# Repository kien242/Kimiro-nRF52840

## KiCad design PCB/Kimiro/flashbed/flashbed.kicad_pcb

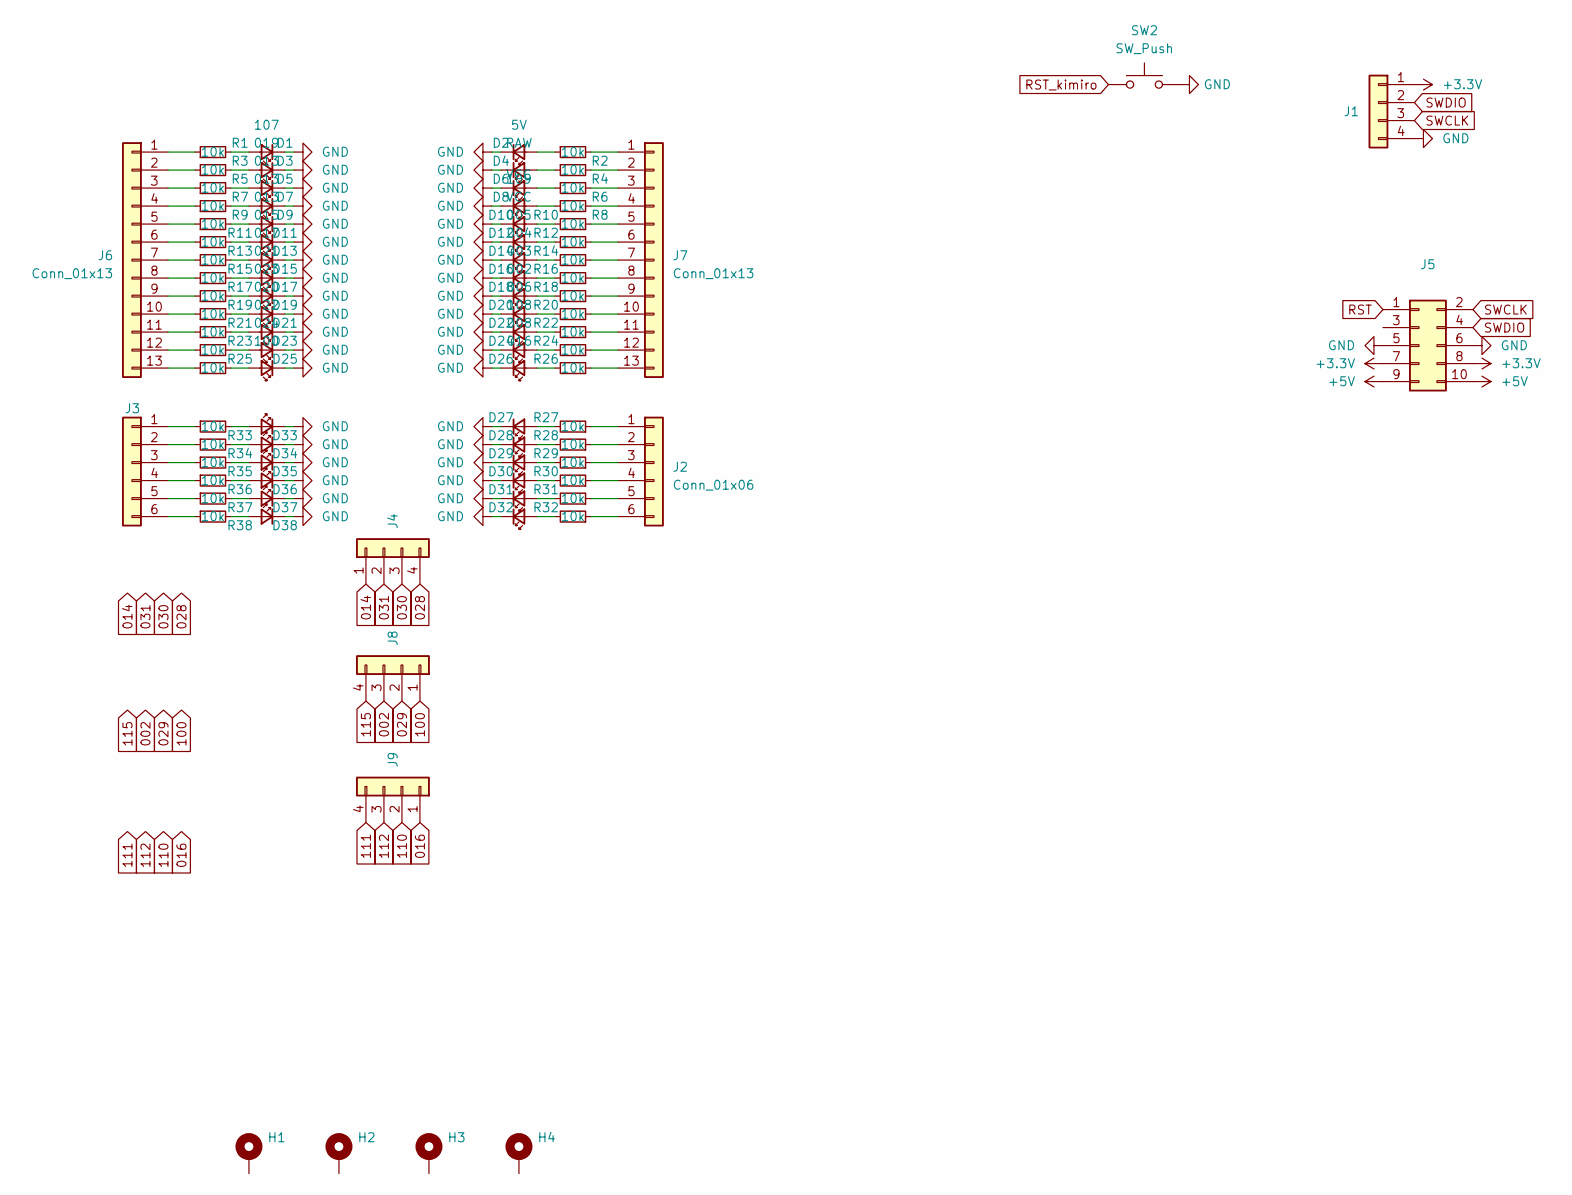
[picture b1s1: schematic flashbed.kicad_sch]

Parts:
D1: 107; LED_0603_1608Metric_Pad1.05x0.95mm_HandSolder
D2: 5V; LED_0603_1608Metric_Pad1.05x0.95mm_HandSolder
D3: 019; LED_0603_1608Metric_Pad1.05x0.95mm_HandSolder
D4: RAW; LED_0603_1608Metric_Pad1.05x0.95mm_HandSolder
D5, D7, D9: 013; LED_0603_1608Metric_Pad1.05x0.95mm_HandSolder
D6, D10: VCC; LED_0603_1608Metric_Pad1.05x0.95mm_HandSolder
D8: 109; LED_0603_1608Metric_Pad1.05x0.95mm_HandSolder
D11: 015; LED_0603_1608Metric_Pad1.05x0.95mm_HandSolder
D12: 005; LED_0603_1608Metric_Pad1.05x0.95mm_HandSolder
D13: 017; LED_0603_1608Metric_Pad1.05x0.95mm_HandSolder
D14: 004; LED_0603_1608Metric_Pad1.05x0.95mm_HandSolder
D15: 021; LED_0603_1608Metric_Pad1.05x0.95mm_HandSolder
D16: 003; LED_0603_1608Metric_Pad1.05x0.95mm_HandSolder
D17: 023; LED_0603_1608Metric_Pad1.05x0.95mm_HandSolder
D18: 002; LED_0603_1608Metric_Pad1.05x0.95mm_HandSolder
D19: 020; LED_0603_1608Metric_Pad1.05x0.95mm_HandSolder
D20: 006; LED_0603_1608Metric_Pad1.05x0.95mm_HandSolder
D21: 022; LED_0603_1608Metric_Pad1.05x0.95mm_HandSolder
D22: 108; LED_0603_1608Metric_Pad1.05x0.95mm_HandSolder
D23: 024; LED_0603_1608Metric_Pad1.05x0.95mm_HandSolder
D24: 008; LED_0603_1608Metric_Pad1.05x0.95mm_HandSolder
D25: 100; LED_0603_1608Metric_Pad1.05x0.95mm_HandSolder
D26: 016; LED_0603_1608Metric_Pad1.05x0.95mm_HandSolder
D27, D28, D29, D30, D31, D32, D33, D34, D35, D36, D37, D38: LED_0603_1608Metric_Pad1.05x0.95mm_HandSolder
H1, H2, H3, H4: MountingHole_3.2mm_M3_Pad_Via
J1, J4, J8, J9: PinHeader_1x04_P2.54mm_Vertical_P75-B1
J2: Conn_01x06; PinHeader_1x06_P2.54mm_Vertical
J3: PinHeader_1x06_P2.54mm_Vertical
J5: IDC-Header_2x05_P2.54mm_Horizontal
J6, J7: Conn_01x13; PinHeader_1x13_P2.54mm_Vertical
R1, R2, R3, R4, R5, R6, R7, R8, R9, R10, R11, R12, R13, R14, R15, R16, R17, R18, R19, R20, R21, R22, R23, R24, R25, R26, R27, R28, R29, R30, R31, R32, R33, R34, R35, R36, R37, R38: 10k; R_0603_1608Metric_Pad0.98x0.95mm_HandSolder
SW2: SW_Push; SW_SPST_TL3342

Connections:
002: J8.3
014: J4.1
016: J9.1
028: J4.4
029: J8.2
030: J4.3
031: J4.2
100: J8.1
110: J9.2
111: J9.4
112: J9.3
115: J8.4
+3V3: J1.1, J5.7, J5.8
+5V: J5.9, J5.10
GND: D1.1 (K), D2.1 (K), D3.1 (K), D4.1 (K), D5.1 (K), D6.1 (K), D7.1 (K), D8.1 (K), D9.1 (K), D10.1 (K), D11.1 (K), D12.1 (K), D13.1 (K), D14.1 (K), D15.1 (K), D16.1 (K), D17.1 (K), D18.1 (K), D19.1 (K), D20.1 (K), D21.1 (K), D22.1 (K), D23.1 (K), D24.1 (K), D25.1 (K), D26.1 (K), D27.1 (K), D28.1 (K), D29.1 (K), D30.1 (K), D31.1 (K), D32.1 (K), D33.1 (K), D34.1 (K), D35.1 (K), D36.1 (K), D37.1 (K), D38.1 (K), J1.4, J5.5, J5.6, SW2.2
unnamed: D1.2 (A), R1.2
unnamed: D2.2 (A), R2.1
unnamed: D3.2 (A), R3.2
unnamed: D4.2 (A), R4.1
unnamed: D5.2 (A), R5.2
unnamed: D6.2 (A), R6.1
unnamed: D7.2 (A), R7.2
unnamed: D8.2 (A), R8.1
unnamed: D9.2 (A), R9.2
unnamed: D10.2 (A), R10.2
unnamed: D11.2 (A), R11.2
unnamed: D12.2 (A), R12.2
unnamed: D13.2 (A), R13.2
unnamed: D14.2 (A), R14.2
unnamed: D15.2 (A), R15.2
unnamed: D16.2 (A), R16.2
unnamed: D17.2 (A), R17.2
unnamed: D18.2 (A), R18.2
unnamed: D19.2 (A), R19.2
unnamed: D20.2 (A), R20.2
unnamed: D21.2 (A), R21.2
unnamed: D22.2 (A), R22.2
unnamed: D23.2 (A), R23.2
unnamed: D24.2 (A), R24.2
unnamed: D25.2 (A), R25.2
unnamed: D26.2 (A), R26.2
unnamed: D27.2 (A), R27.2
unnamed: D28.2 (A), R28.2
unnamed: D29.2 (A), R29.2
unnamed: D30.2 (A), R30.2
unnamed: D31.2 (A), R31.2
unnamed: D32.2 (A), R32.2
unnamed: D33.2 (A), R33.2
unnamed: D34.2 (A), R34.2
unnamed: D35.2 (A), R35.2
unnamed: D36.2 (A), R36.2
unnamed: D37.2 (A), R37.2
unnamed: D38.2 (A), R38.2
unnamed: J2.1, R27.1
unnamed: J2.2, R28.1
unnamed: J2.3, R29.1
unnamed: J2.4, R30.1
unnamed: J2.5, R31.1
unnamed: J2.6, R32.1
unnamed: J3.1, R33.1
unnamed: J3.2, R34.1
unnamed: J3.3, R35.1
unnamed: J3.4, R36.1
unnamed: J3.5, R37.1
unnamed: J3.6, R38.1
unnamed: J6.1, R1.1
unnamed: J6.2, R3.1
unnamed: J6.3, R5.1
unnamed: J6.4, R7.1
unnamed: J6.5, R9.1
unnamed: J6.6, R11.1
unnamed: J6.7, R13.1
unnamed: J6.8, R15.1
unnamed: J6.9, R17.1
unnamed: J6.10, R19.1
unnamed: J6.11, R21.1
unnamed: J6.12, R23.1
unnamed: J6.13, R25.1
unnamed: J7.1, R2.2
unnamed: J7.2, R4.2
unnamed: J7.3, R6.2
unnamed: J7.4, R8.2
unnamed: J7.5, R10.1
unnamed: J7.6, R12.1
unnamed: J7.7, R14.1
unnamed: J7.8, R16.1
unnamed: J7.9, R18.1
unnamed: J7.10, R20.1
unnamed: J7.11, R22.1
unnamed: J7.12, R24.1
unnamed: J7.13, R26.1
RST: J5.1
RST_kimiro: SW2.1
SWCLK: J1.3, J5.2
SWDIO: J1.2, J5.4

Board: 2 copper layers, 129 parts (0 on the bottom side), 81 nets, no tracks yet.

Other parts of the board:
kibuzzard-62FFA9FF: G***; kibuzzard-62FFA9FF
kibuzzard-62FFAA5B, kibuzzard-62FFAA5B#2: G***; kibuzzard-62FFAA5B
kibuzzard-62FFAA07, kibuzzard-62FFAA07#2: G***; kibuzzard-62FFAA07
kibuzzard-62FFAA9F: G***; kibuzzard-62FFAA9F
kibuzzard-62FFAA43, kibuzzard-62FFAA43#2: G***; kibuzzard-62FFAA43
kibuzzard-62FFAA85: G***; kibuzzard-62FFAA85
kibuzzard-62FFAAD6, kibuzzard-62FFAAD6#2: G***; kibuzzard-62FFAAD6
kibuzzard-62FFAAE6, kibuzzard-62FFAAE6#2: G***; kibuzzard-62FFAAE6
kibuzzard-64036B7A: G***; kibuzzard-64036B7A
kibuzzard-640356F0: G***; kibuzzard-640356F0
kibuzzard-640359A3, kibuzzard-640359A3#2: G***; kibuzzard-640359A3
kibuzzard-640359AA, kibuzzard-640359AA#2: G***; kibuzzard-640359AA
kibuzzard-640359B0, kibuzzard-640359B0#2: G***; kibuzzard-640359B0
kibuzzard-640359B7: G***; kibuzzard-640359B7
kibuzzard-640359BC: G***; kibuzzard-640359BC
kibuzzard-6403595A: G***; kibuzzard-6403595A
kibuzzard-6403597E, kibuzzard-6403597E#2: G***; kibuzzard-6403597E
kibuzzard-6403599D, kibuzzard-6403599D#2: G***; kibuzzard-6403599D
kibuzzard-64035962: G***; kibuzzard-64035962
kibuzzard-64035969: G***; kibuzzard-64035969
kibuzzard-64035970: G***; kibuzzard-64035970
kibuzzard-64035979, kibuzzard-64035979#2: G***; kibuzzard-64035979
kibuzzard-64035984, kibuzzard-64035984#2: G***; kibuzzard-64035984
kibuzzard-64035989, kibuzzard-64035989#2: G***; kibuzzard-64035989
kibuzzard-64035993, kibuzzard-64035993#2: G***; kibuzzard-64035993

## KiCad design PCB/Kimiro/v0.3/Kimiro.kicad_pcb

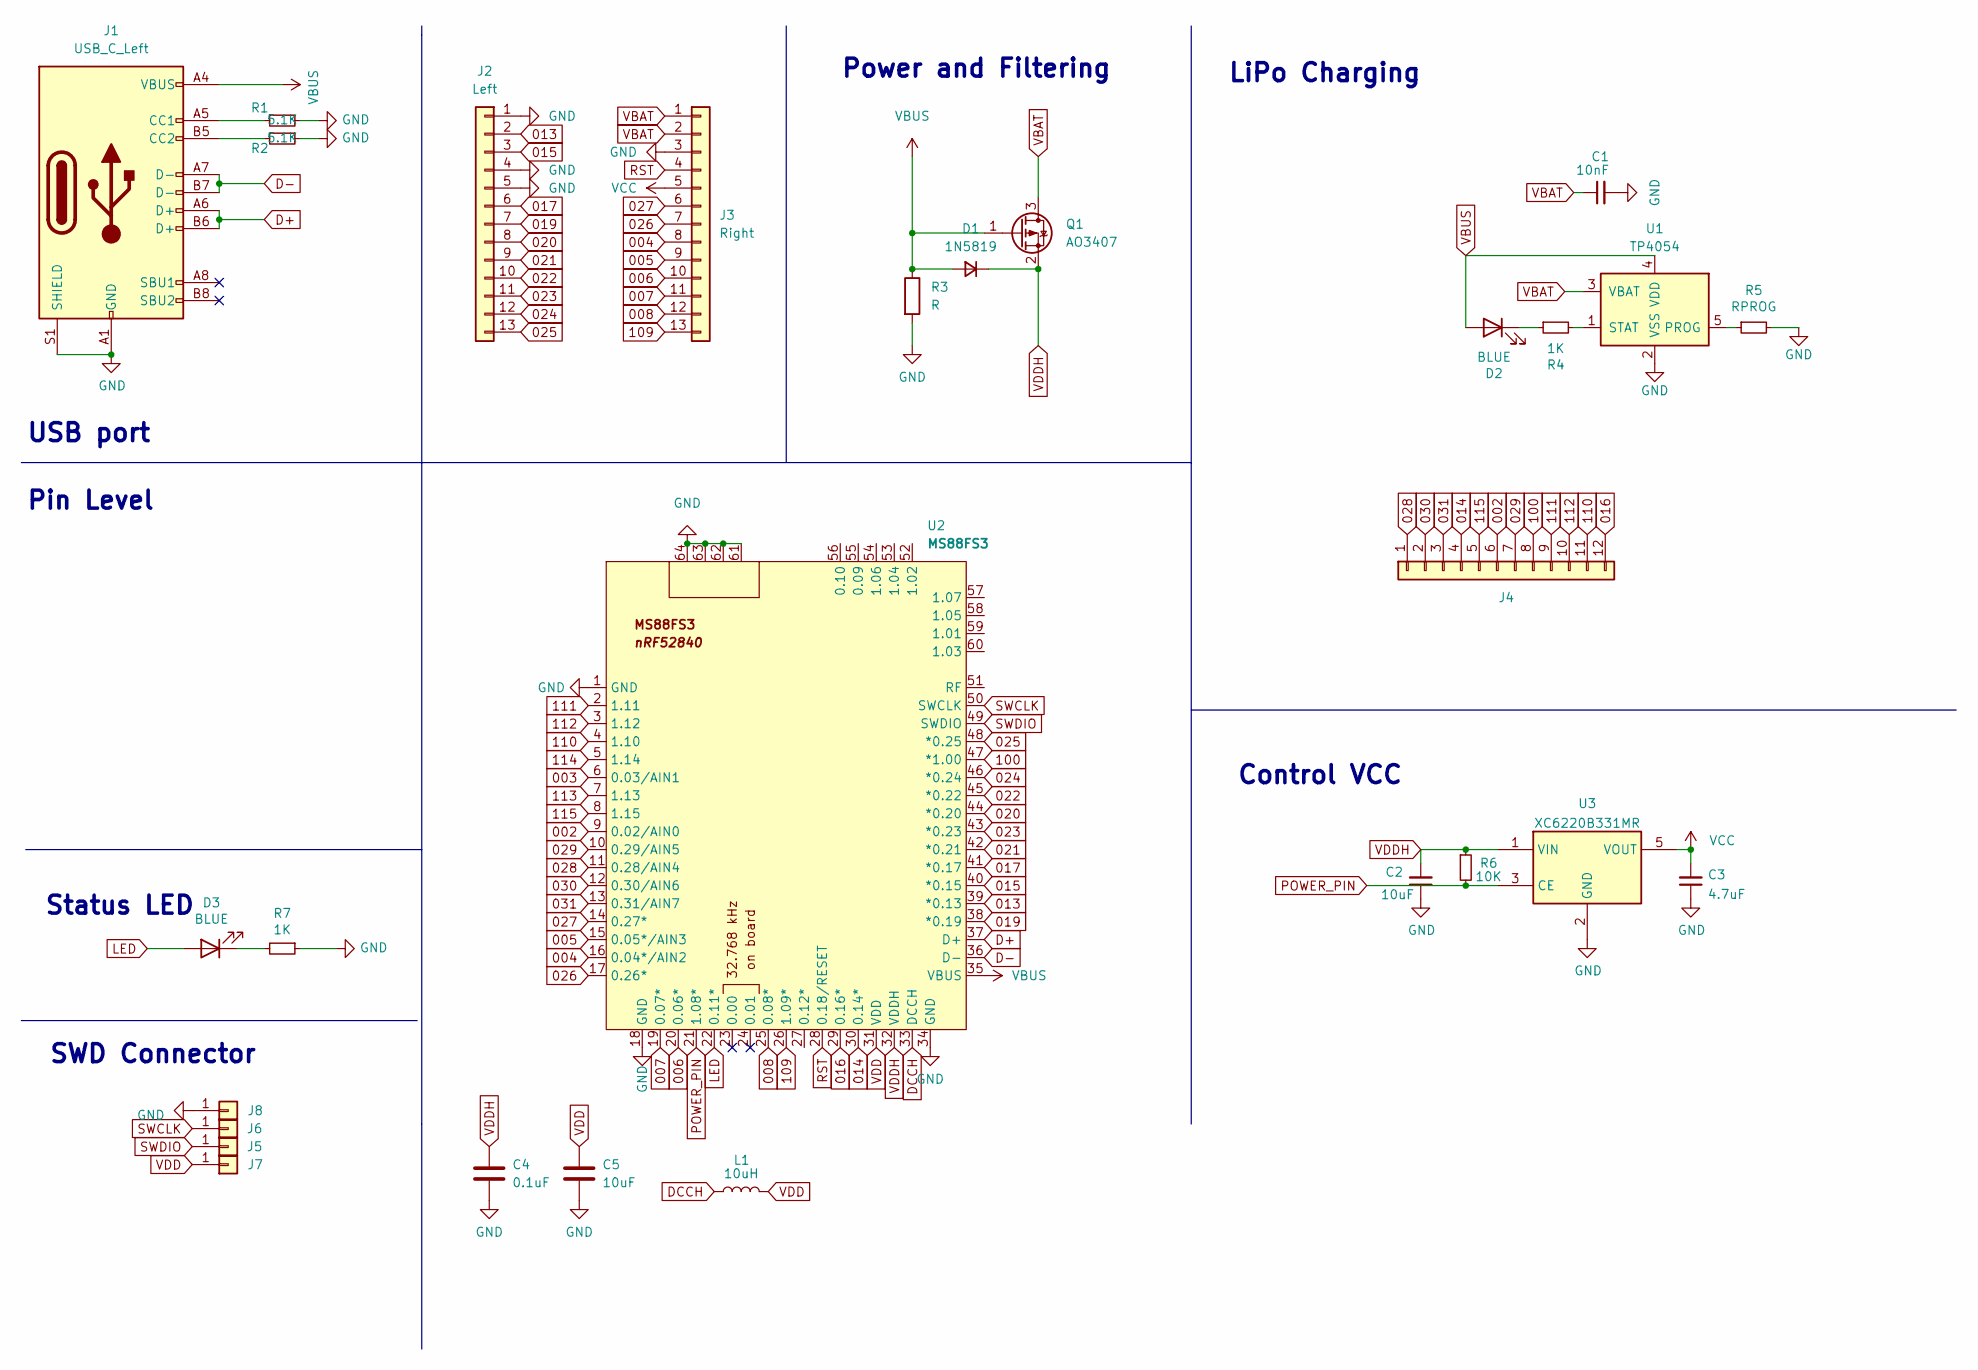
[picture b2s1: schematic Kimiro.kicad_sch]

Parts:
C1: 10nF; C_0402_1005Metric
C2: 10uF; C_0402_1005Metric; Manufacturer Part CL10A106KP8NNNC; LCSC Part C19702
C3: 4.7uF; C_0402_1005Metric; Manufacturer Part CL05A475KP5NRNC; LCSC Part C368809
C4: 0.1uF; C_0402_1005Metric
C5: 10uF; C_0402_1005Metric
D1: 1N5819; D_SOD-323
D2, D3: BLUE; LED_0603_1608Metric; LCSC Part Number C375446
J1: USB_C_Left; USB-C-Low
J2: Left; Conn_1x13_P2.54mm
J3: Right; Conn_1x13_P2.54mm
J4: Conn
J5, J6, J7, J8: Conn_1x01
L1: 10uH; L_0603_1608Metric
Q1: AO3407; SOT-23
R1, R2: 5.1K; R_0402_1005Metric
R3: R; R_0402_1005Metric
R4: 1K; R_0402_1005Metric
R5: RPROG; R_0402_1005Metric
R6: 10K; R_0402_1005Metric; Manufacturer Part RC0402FR-0710KL; LCSC Part C60490
R7: 1K; R_0402_1005Metric; LCSC Part Number C21190
U1: TP4054; SOT-23-5
U2: MS88FS3; MODULE_MS88SF3
U3: XC6220B331MR; SOT-23-5; Manufacturer Part XC6220B331MR-G‎; Digikey 893-1133-1-ND‎

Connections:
002: J4.6, U2.9 (0.02/AIN0)
003: U2.6 (0.03/AIN1)
004: J3.8, U2.16 (0.04*/AIN2)
005: J3.9, U2.15 (0.05*/AIN3)
006: J3.10, U2.20 (0.06*)
007: J3.11, U2.19 (0.07*)
008: J3.12, U2.25 (0.08*)
013: J2.2, U2.39 (*0.13)
014: J4.4, U2.30 (0.14*)
015: J2.3, U2.40 (*0.15)
016: J4.12, U2.29 (0.16*)
017: J2.6, U2.41 (*0.17)
019: J2.7, U2.38 (*0.19)
020: J2.8, U2.44 (*0.20)
021: J2.9, U2.42 (*0.21)
022: J2.10, U2.45 (*0.22)
023: J2.11, U2.43 (*0.23)
024: J2.12, U2.46 (*0.24)
025: J2.13, U2.48 (*0.25)
026: J3.7, U2.17 (0.26*)
027: J3.6, U2.14 (0.27*)
028: J4.1, U2.11 (0.28/AIN4)
029: J4.7, U2.10 (0.29/AIN5)
030: J4.2, U2.12 (0.30/AIN6)
031: J4.3, U2.13 (0.31/AIN7)
100: J4.8, U2.47 (*1.00)
109: J3.13, U2.26 (1.09*)
110: J4.11, U2.4 (1.10)
111: J4.9, U2.2 (1.11)
112: J4.10, U2.3 (1.12)
113: U2.7 (1.13)
114: U2.5 (1.14)
115: J4.5, U2.8 (1.15)
D+: J1.A6 (D+), J1.B6 (D+), U2.37 (D+)
D-: J1.A7 (D-), J1.B7 (D-), U2.36 (D-)
DCCH: L1.1, U2.33 (DCCH)
GND: C1.2, C2.1, C3.1, C4.2, C5.2, J1.A1 (GND), J1.A12 (GND), J1.B1 (GND), J1.B12 (GND), J1.S1 (SHIELD), J2.1, J2.4, J2.5, J3.3, J8.1, R1.2, R2.1, R3.2, R5.2, R7.1, U1.2 (VSS), U2.1 (GND), U2.18 (GND), U2.34 (GND), U2.61, U2.62, U2.63, U2.64, U3.2 (GND)
LED: D3.2 (A), U2.22 (0.11*)
unnamed: D2.1 (K), R4.1
unnamed: D3.1 (K), R7.2
unnamed: J1.A5 (CC1), R1.1
unnamed: J1.B5 (CC2), R2.2
unnamed: R5.1, U1.5 (PROG)
unnamed: R4.2, U1.1 (STAT)
POWER_PIN: R6.2, U2.21 (1.08*), U3.3 (CE)
RST: J3.4, U2.28 (0.18/RESET)
SWCLK: J6.1, U2.50 (SWCLK)
SWDIO: J5.1, U2.49 (SWDIO)
VBAT: C1.1, J3.1, J3.2, Q1.3 (D), U1.3 (VBAT)
VBUS: D1.2 (A), D2.2 (A), J1.A4 (VBUS), J1.A9 (VBUS), J1.B4 (VBUS), J1.B9 (VBUS), Q1.1 (G), R3.1, U1.4 (VDD), U2.35 (VBUS)
VCC: C3.2, J3.5, U3.5 (VOUT)
VDD: C5.1, J7.1, L1.2, U2.31 (VDD)
VDDH: C2.2, C4.1, D1.1 (K), Q1.2 (S), R6.1, U2.32 (VDDH), U3.1 (VIN)

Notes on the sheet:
Power and Filtering
Status LED
LiPo Charging
Control VCC
Pin Level
SWD Connector
USB port

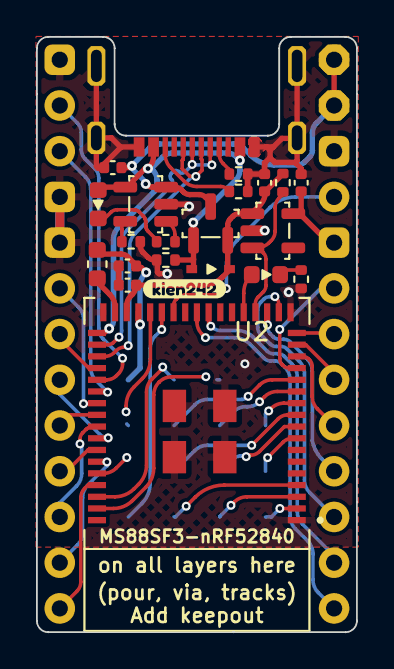
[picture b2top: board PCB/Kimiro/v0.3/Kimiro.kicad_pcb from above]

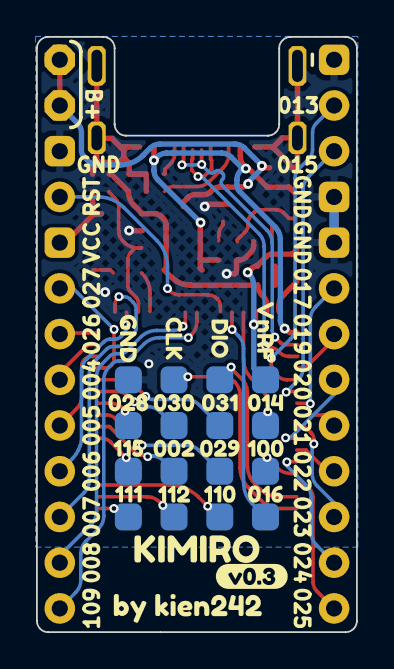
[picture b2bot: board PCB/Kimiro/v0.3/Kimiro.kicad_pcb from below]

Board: 2 copper layers, 17.8 x 33.1 mm, 48 parts (24 on the bottom side), 50 nets.

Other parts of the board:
kibuzzard-62E2A6C4: G***; kibuzzard-62E2A6C4
kibuzzard-62E24B57: G***; kibuzzard-62E24B57
kibuzzard-63BCF8A2: G***; kibuzzard-63BCF8A2
kibuzzard-63BCF8A9: G***; kibuzzard-63BCF8A9
kibuzzard-63BCF8C7: G***; kibuzzard-63BCF8C7
kibuzzard-635CB1F2: G***; kibuzzard-635CB1F1
kibuzzard-635CFC2D: G***; kibuzzard-635CFC2D
kibuzzard-635CFC3A: G***; kibuzzard-635CFC3A
kibuzzard-635CFC4F: G***; kibuzzard-635CFC4F
kibuzzard-635CFC5E: G***; kibuzzard-635CFC5E
kibuzzard-635CFC26: G***; kibuzzard-635CFC26
kibuzzard-635CFC34: G***; kibuzzard-635CFC34
kibuzzard-635CFC40: G***; kibuzzard-635CFC40
kibuzzard-635CFC48: G***; kibuzzard-635CFC48
kibuzzard-635CFC57: G***; kibuzzard-635CFC57
kibuzzard-635CFC63: G***; kibuzzard-635CFC63
kibuzzard-635CFC69: G***; kibuzzard-635CFC69
kibuzzard-635D09C5: G***; kibuzzard-635D09C5
kibuzzard-64034CD4: G***; kibuzzard-64034CD4
kibuzzard-640324C5: G***; kibuzzard-640324C5

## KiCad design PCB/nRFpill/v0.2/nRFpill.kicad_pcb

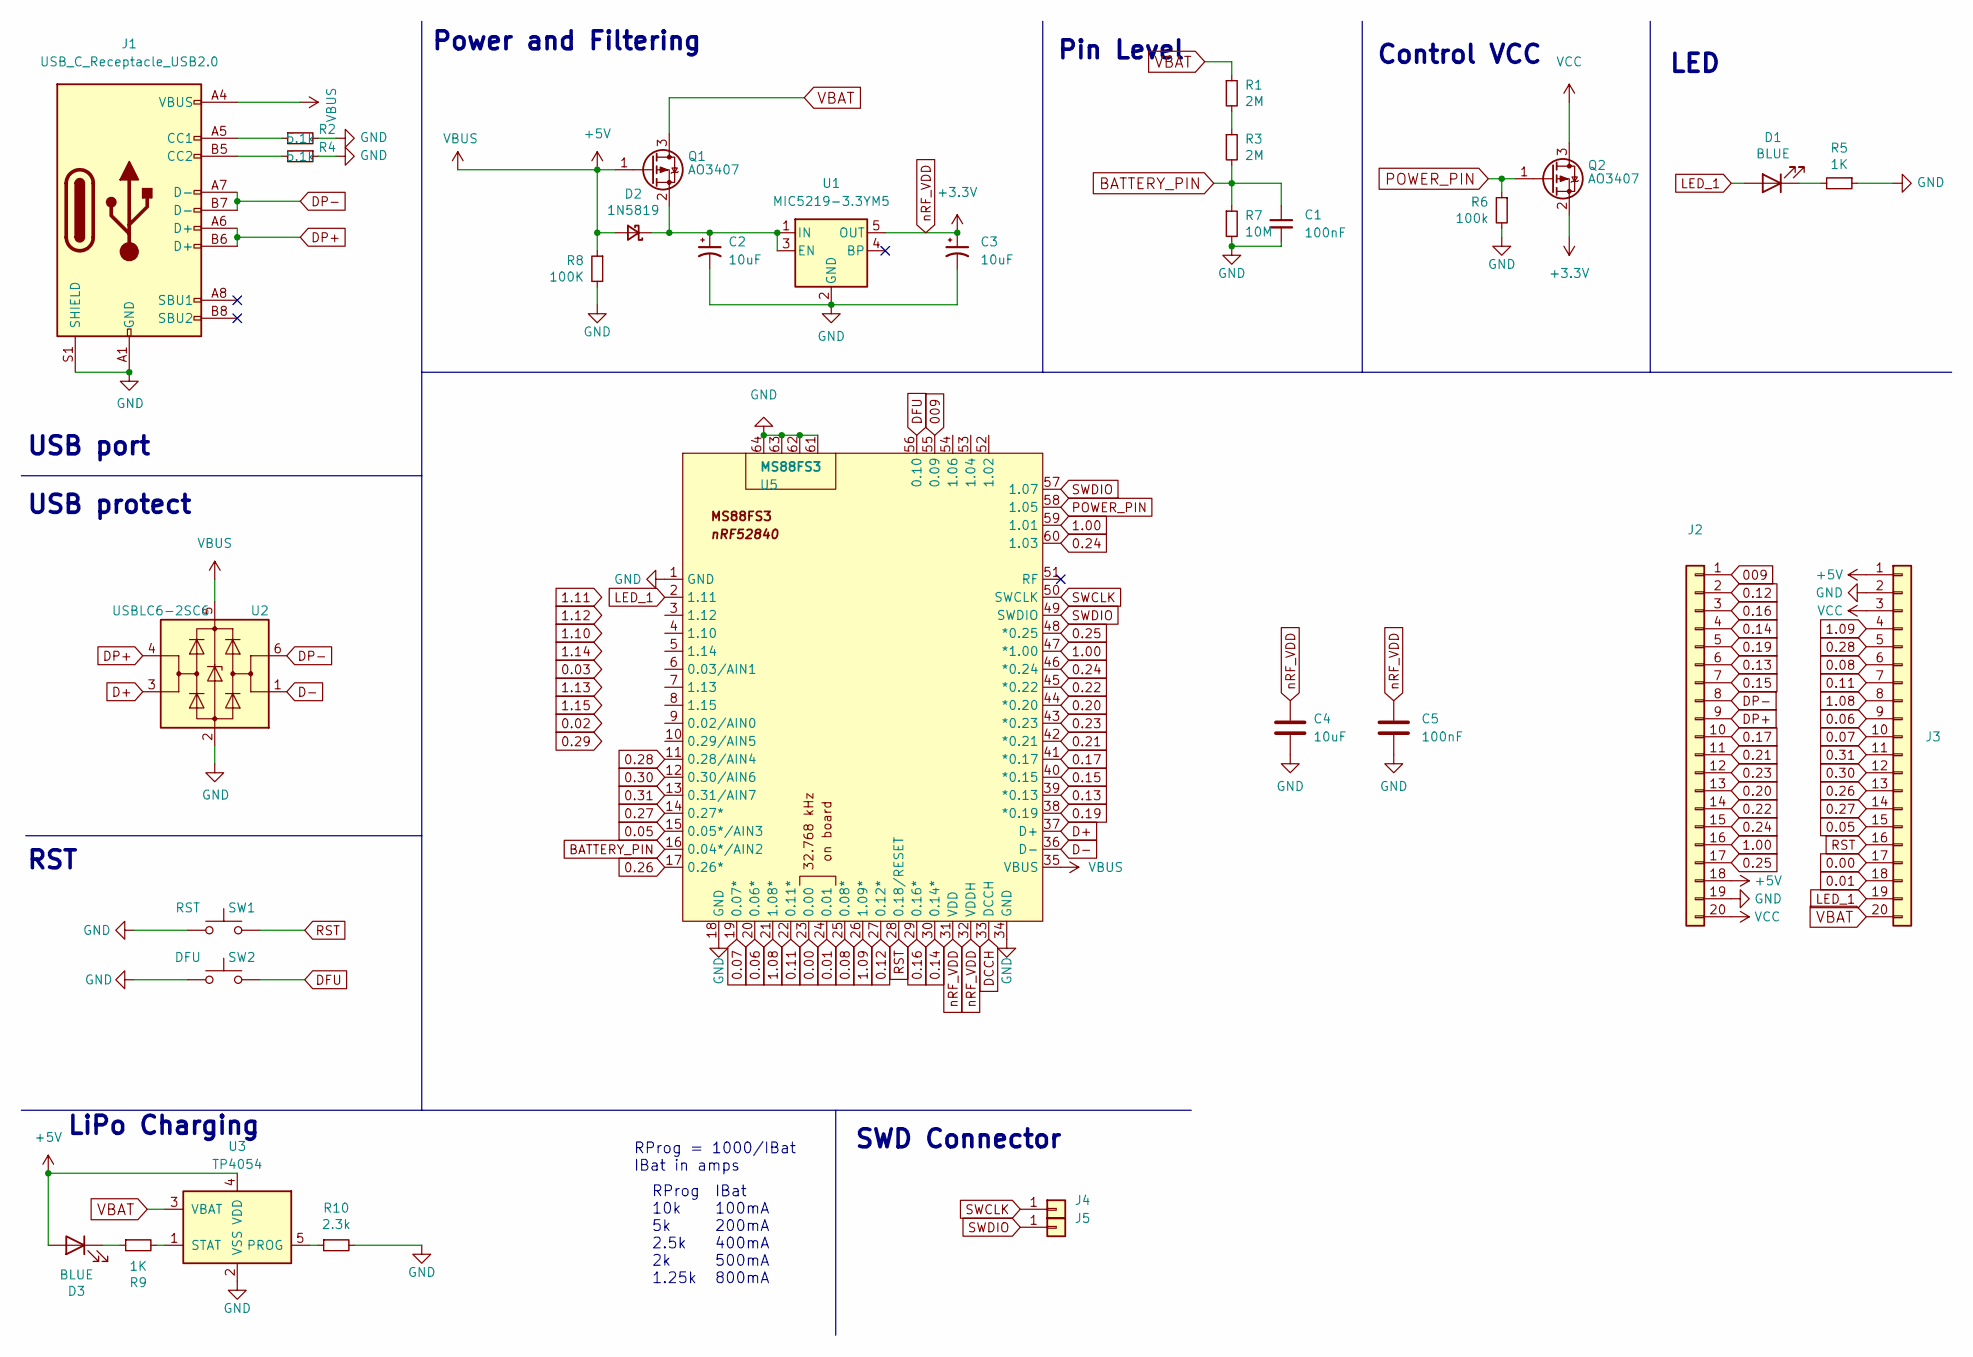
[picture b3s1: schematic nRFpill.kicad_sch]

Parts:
C1, C5: 100nF; C_0603_1608Metric
C2, C3: 10uF; CP_EIA-3216-12_Kemet-S
C4: 10uF; C_0603_1608Metric
D1, D3: BLUE; LED_0603_1608Metric; LCSC Part Number C375446
D2: 1N5819; D_SOD-323_HandSoldering
J1: USB_C_Receptacle_USB2.0; USB-C-Low
J2, J3: PinHeader_1x20_P2.54mm_Vertical
J4: TestPoint_Pad_1.5x1.5mm
J5: TestPoint_Pad_D1.5mm
Q1, Q2: AO3407; SOT-23
R1, R3: 2M; R_0603_1608Metric
R2, R4: 5.1k; R_0603_1608Metric
R5: 1K; R_0603_1608Metric; LCSC Part Number C21190
R6: 100k; R_0603_1608Metric
R7: 10M; R_0603_1608Metric
R8: 100K; R_0603_1608Metric
R9: 1K; R_0603_1608Metric
R10: 2.3k; R_0603_1608Metric
SW1: RST; SW_SPST_B3U-1000P
SW2: DFU; SW_SPST_B3U-1000P
U1: MIC5219-3.3YM5; SOT-23-5
U2: USBLC6-2SC6; SOT-23-6
U3: TP4054; SOT-23-5
U5: MS88FS3; MODULE_MS88SF3

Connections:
0.00: J3.17, U5.23 (0.00)
0.01: J3.18, U5.24 (0.01)
0.05: J3.15, U5.15 (0.05*/AIN3)
0.06: J3.9, U5.20 (0.06*)
0.07: J3.10, U5.19 (0.07*)
0.08: J3.6, U5.25 (0.08*)
0.11: J3.7, U5.22 (0.11*)
0.12: J2.2, U5.27 (0.12*)
0.13: J2.6, U5.39 (*0.13)
0.14: J2.4, U5.30 (0.14*)
0.15: J2.7, U5.40 (*0.15)
0.16: J2.3, U5.29 (0.16*)
0.17: J2.10, U5.41 (*0.17)
0.19: J2.5, U5.38 (*0.19)
0.20: J2.13, U5.44 (*0.20)
0.21: J2.11, U5.42 (*0.21)
0.22: J2.14, U5.45 (*0.22)
0.23: J2.12, U5.43 (*0.23)
0.24: J2.15, U5.46 (*0.24), U5.60 (1.03)
0.25: J2.17, U5.48 (*0.25)
0.26: J3.13, U5.17 (0.26*)
0.27: J3.14, U5.14 (0.27*)
0.28: J3.5, U5.11 (0.28/AIN4)
0.30: J3.12, U5.12 (0.30/AIN6)
0.31: J3.11, U5.13 (0.31/AIN7)
1.00: J2.16, U5.47 (*1.00), U5.59 (1.01)
1.08: J3.8, U5.21 (1.08*)
1.09: J3.4, U5.26 (1.09*)
009: J2.1, U5.55 (0.09)
+5V: D2.2 (A), D3.2 (A), J1.A4 (VBUS), J1.A9 (VBUS), J1.B4 (VBUS), J1.B9 (VBUS), J2.18, J3.1, Q1.1 (G), R8.1, U2.5 (VBUS), U3.4 (VDD), U5.35 (VBUS)
BATTERY_PIN: C1.1, R3.2, R7.1, U5.16 (0.04*/AIN2)
D+: U2.3 (I/O2), U5.37 (D+)
D-: U2.1 (I/O1), U5.36 (D-)
DCCH: U5.33 (DCCH)
DFU: SW2.2, U5.56 (0.10)
DP+: J1.A6 (D+), J1.B6 (D+), J2.9, U2.4 (I/O2)
DP-: J1.A7 (D-), J1.B7 (D-), J2.8, U2.6 (I/O1)
GND: C1.2, C2.2, C3.2, C4.2, C5.2, J1.A1 (GND), J1.A12 (GND), J1.B1 (GND), J1.B12 (GND), J1.S1 (SHIELD), J2.19, J3.2, R2.2, R4.1, R5.1, R6.2, R7.2, R8.2, R10.2, SW1.1, SW2.1, U1.2 (GND), U2.2 (GND), U3.2 (VSS), U5.1 (GND), U5.18 (GND), U5.34 (GND), U5.61, U5.62, U5.63, U5.64
LED_1: D1.2 (A), J3.19, U5.2 (1.11)
unnamed: C2.1, D2.1 (K), Q1.2 (S), U1.1 (IN), U1.3 (EN)
unnamed: D1.1 (K), R5.2
unnamed: D3.1 (K), R9.1
unnamed: J1.A5 (CC1), R2.1
unnamed: J1.B5 (CC2), R4.2
unnamed: R1.2, R3.1
unnamed: R9.2, U3.1 (STAT)
unnamed: R10.1, U3.5 (PROG)
POWER_PIN: Q2.1 (G), R6.1, U5.58 (1.05)
RST: J3.16, SW1.2, U5.28 (0.18/RESET)
SWCLK: J4.1, U5.50 (SWCLK)
SWDIO: J5.1, U5.49 (SWDIO), U5.57 (1.07)
VBAT: J3.20, Q1.3 (D), R1.1, U3.3 (VBAT)
VCC: J2.20, J3.3, Q2.3 (D)
nRF_VDD: C3.1, C4.1, C5.1, Q2.2 (S), U1.5 (OUT), U5.31 (VDD), U5.32 (VDDH)

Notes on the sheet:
Control VCC
RProg 10k 5k 2.5k 2k 1.25k
RST
RProg = 1000/IBat IBat in amps
LED
Power and Filtering
USB protect
IBat 100mA 200mA 400mA 500mA 800mA
LiPo Charging
USB port
Pin Level
SWD Connector

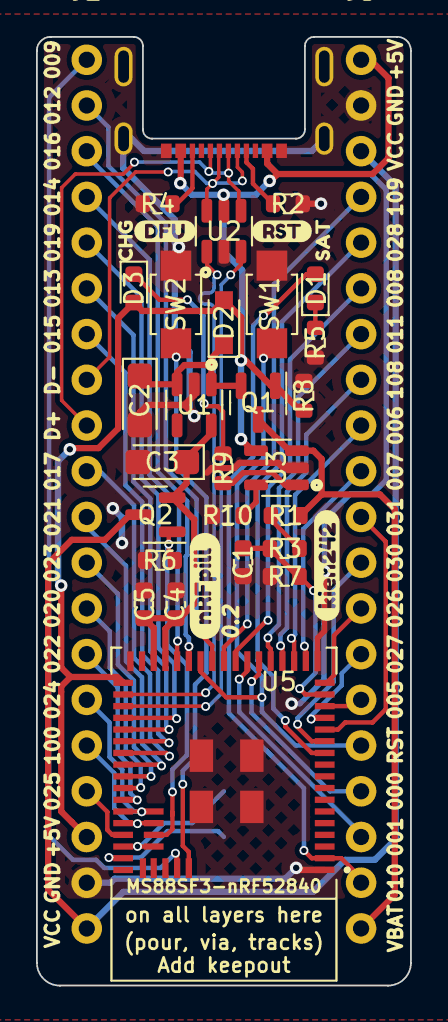
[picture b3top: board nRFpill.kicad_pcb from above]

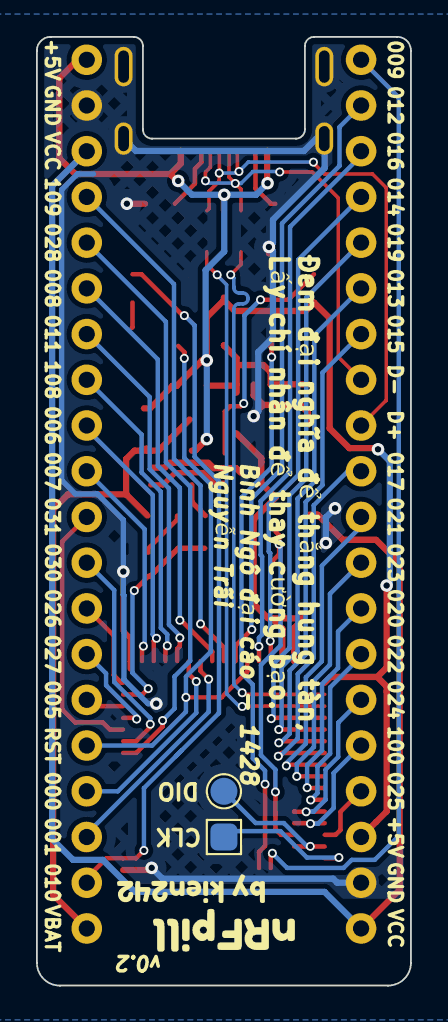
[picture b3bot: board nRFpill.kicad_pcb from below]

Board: 2 copper layers, 20.8 x 52.7 mm, 39 parts (4 on the bottom side), 53 nets.

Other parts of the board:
kibuzzard-62FEE3AB: G***; kibuzzard-62FEE3AB
kibuzzard-62FEE358: G***; kibuzzard-62FEE358
kibuzzard-6303CF12: G***; kibuzzard-6303CF12
kibuzzard-6303CF50: G***; kibuzzard-6303CF50
kibuzzard-6303CFD4: G***; kibuzzard-6303CFD4
kibuzzard-6303D094: G***; kibuzzard-6303D094
kibuzzard-63049CD9: G***; kibuzzard-63049CD9
kibuzzard-63049CF8: G***; kibuzzard-63049CF8

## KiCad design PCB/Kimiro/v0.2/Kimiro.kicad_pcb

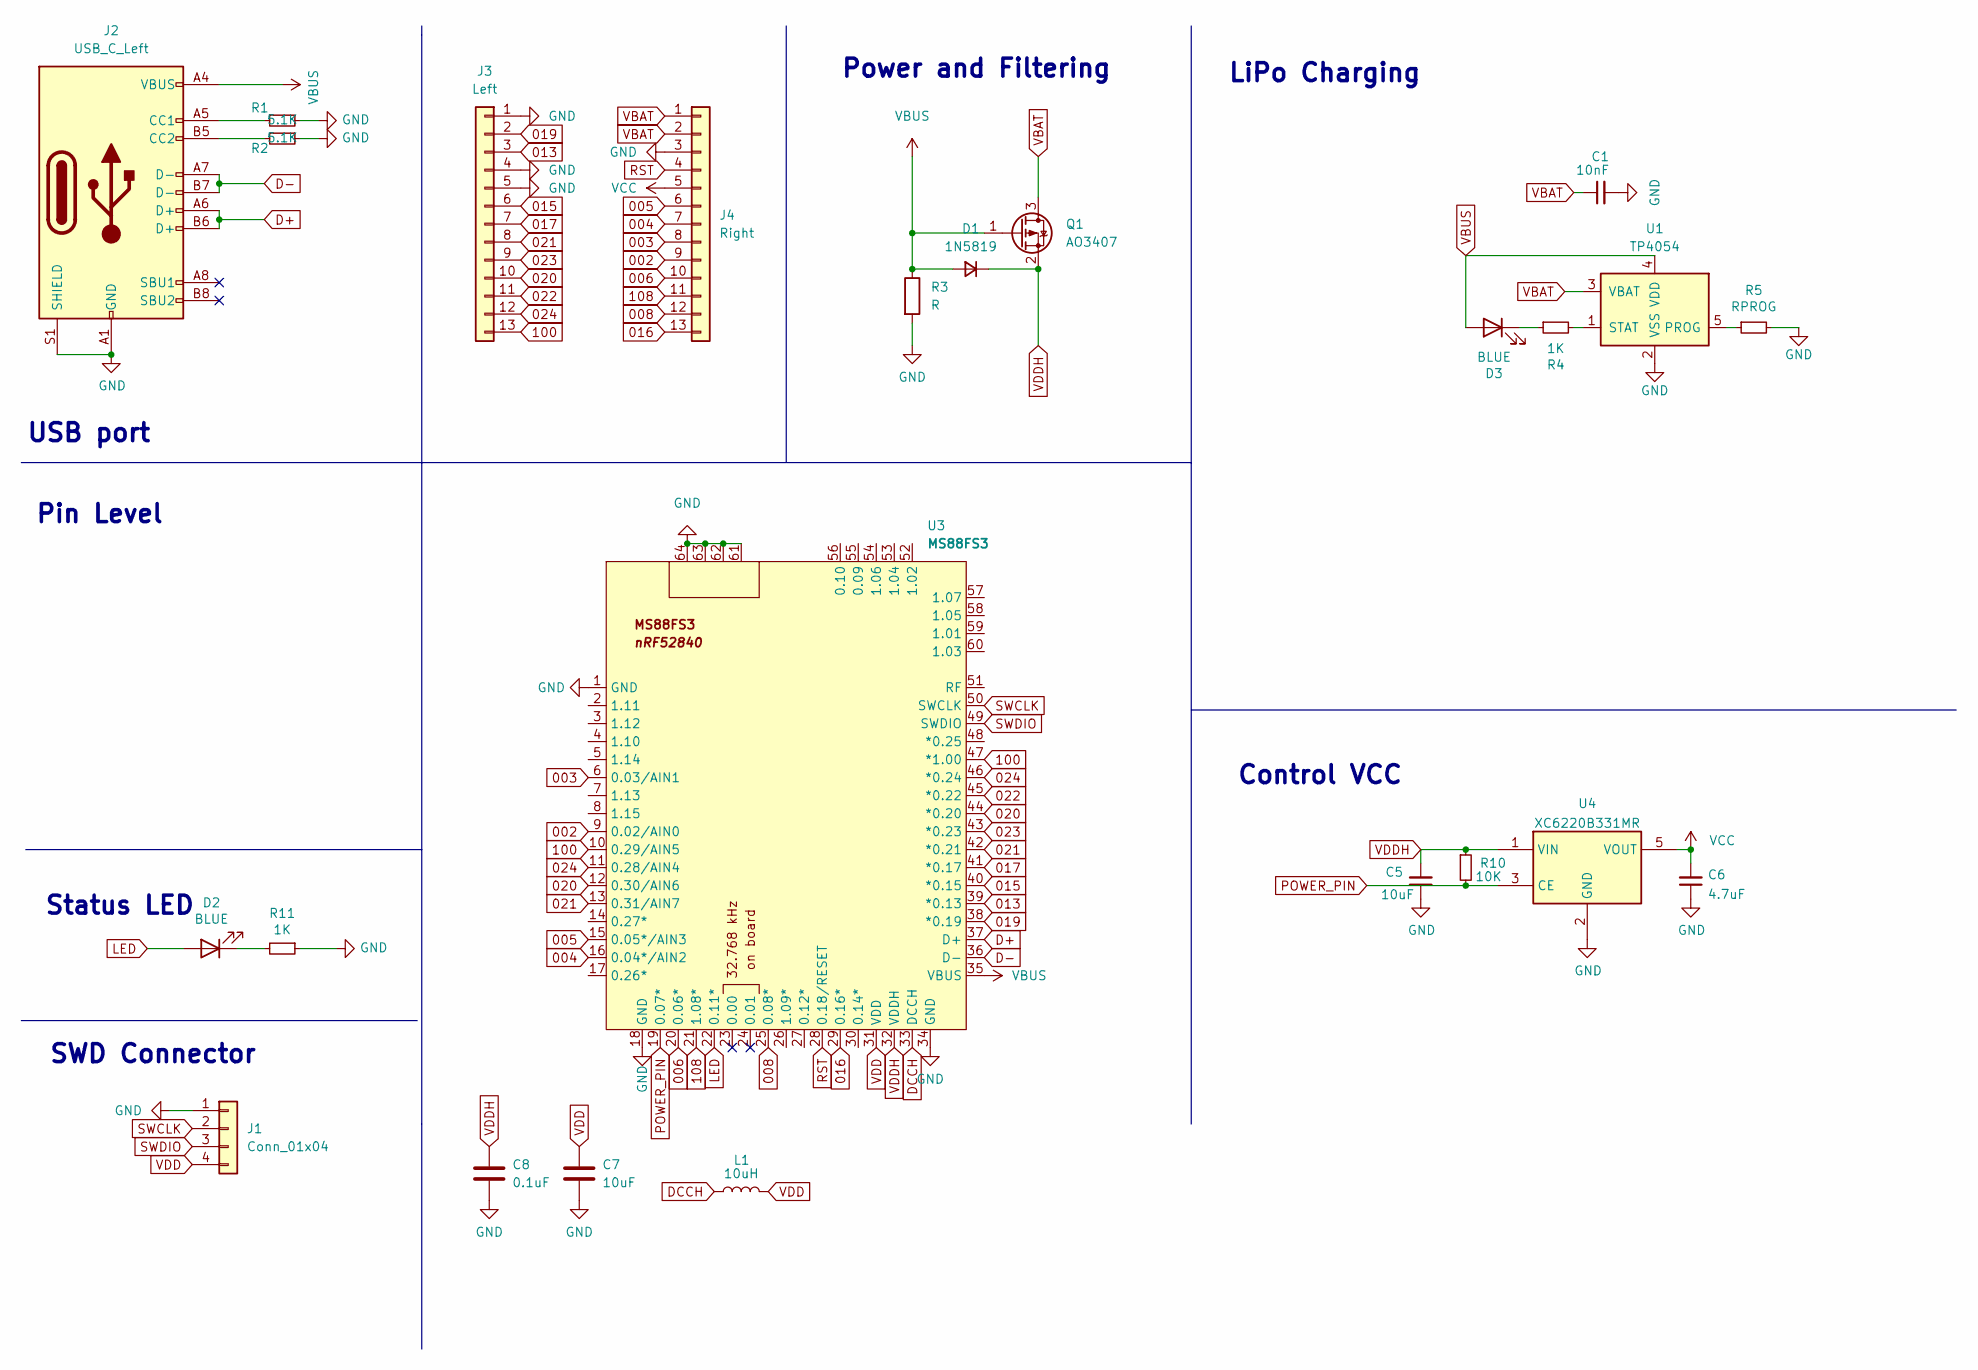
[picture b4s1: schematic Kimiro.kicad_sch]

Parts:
C1: 10nF; C_0402_1005Metric
C5: 10uF; C_0402_1005Metric; Manufacturer Part CL10A106KP8NNNC; LCSC Part C19702
C6: 4.7uF; C_0402_1005Metric; Manufacturer Part CL05A475KP5NRNC; LCSC Part C368809
C7: 10uF; C_0402_1005Metric
C8: 0.1uF; C_0402_1005Metric
D1: 1N5819; D_SOD-323
D2, D3: BLUE; LED_0603_1608Metric; LCSC Part Number C375446
J1: Conn_01x04; Conn_1x04_P2.54mm
J2: USB_C_Left; USB-C-Low
J3: Left; Conn_1x13_P2.54mm
J4: Right; Conn_1x13_P2.54mm
L1: 10uH; L_0603_1608Metric
Q1: AO3407; SOT-23
R1, R2: 5.1K; R_0402_1005Metric
R3: R; R_0402_1005Metric
R4: 1K; R_0402_1005Metric
R5: RPROG; R_0402_1005Metric
R10: 10K; R_0402_1005Metric; Manufacturer Part RC0402FR-0710KL; LCSC Part C60490
R11: 1K; R_0402_1005Metric; LCSC Part Number C21190
U1: TP4054; SOT-23-5
U3: MS88FS3; MS88SF3-nRF52840
U4: XC6220B331MR; SOT-23-5; Manufacturer Part XC6220B331MR-G‎; Digikey 893-1133-1-ND‎

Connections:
002: J4.9, U3.9 (0.02/AIN0)
003: J4.8, U3.6 (0.03/AIN1)
004: J4.7, U3.16 (0.04*/AIN2)
005: J4.6, U3.15 (0.05*/AIN3)
006: J4.10, U3.20 (0.06*)
008: J4.12, U3.25 (0.08*)
013: J3.3, U3.39 (*0.13)
015: J3.6, U3.40 (*0.15)
016: J4.13, U3.29 (0.16*)
017: J3.7, U3.41 (*0.17)
019: J3.2, U3.38 (*0.19)
020: J3.10, U3.12 (0.30/AIN6), U3.44 (*0.20)
021: J3.8, U3.13 (0.31/AIN7), U3.42 (*0.21)
022: J3.11, U3.45 (*0.22)
023: J3.9, U3.43 (*0.23)
024: J3.12, U3.11 (0.28/AIN4), U3.46 (*0.24)
100: J3.13, U3.10 (0.29/AIN5), U3.47 (*1.00)
108: J4.11, U3.21 (1.08*)
D+: J2.A6 (D+), J2.B6 (D+), U3.37 (D+)
D-: J2.A7 (D-), J2.B7 (D-), U3.36 (D-)
DCCH: L1.1, U3.33 (DCCH)
GND: C1.2, C5.1, C6.1, C7.2, C8.2, J1.1, J2.A1 (GND), J2.A12 (GND), J2.B1 (GND), J2.B12 (GND), J2.S1 (SHIELD), J3.1, J3.4, J3.5, J4.3, R1.2, R2.1, R3.2, R5.2, R11.1, U1.2 (VSS), U3.1 (GND), U3.18 (GND), U3.34 (GND), U3.61, U3.62, U3.63, U3.64, U4.2 (GND)
LED: D2.2 (A), U3.22 (0.11*)
unnamed: D2.1 (K), R11.2
unnamed: D3.1 (K), R4.1
unnamed: J2.A5 (CC1), R1.1
unnamed: J2.B5 (CC2), R2.2
unnamed: R4.2, U1.1 (STAT)
unnamed: R5.1, U1.5 (PROG)
POWER_PIN: R10.2, U3.19 (0.07*), U4.3 (CE)
RST: J4.4, U3.28 (0.18/RESET)
SWCLK: J1.2, U3.50 (SWCLK)
SWDIO: J1.3, U3.49 (SWDIO)
VBAT: C1.1, J4.1, J4.2, Q1.3 (D), U1.3 (VBAT)
VBUS: D1.2 (A), D3.2 (A), J2.A4 (VBUS), J2.A9 (VBUS), J2.B4 (VBUS), J2.B9 (VBUS), Q1.1 (G), R3.1, U1.4 (VDD), U3.35 (VBUS)
VCC: C6.2, J4.5, U4.5 (VOUT)
VDD: C7.1, J1.4, L1.2, U3.31 (VDD)
VDDH: C5.2, C8.1, D1.1 (K), Q1.2 (S), R10.1, U3.32 (VDDH), U4.1 (VIN)

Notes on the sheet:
Power and Filtering
Status LED
LiPo Charging
Control VCC
Pin Level
SWD Connector
USB port

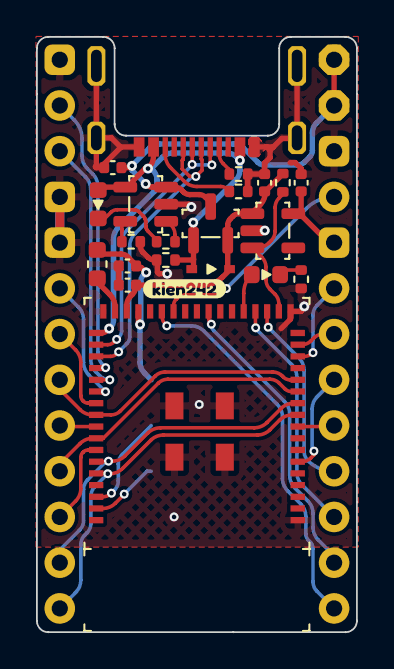
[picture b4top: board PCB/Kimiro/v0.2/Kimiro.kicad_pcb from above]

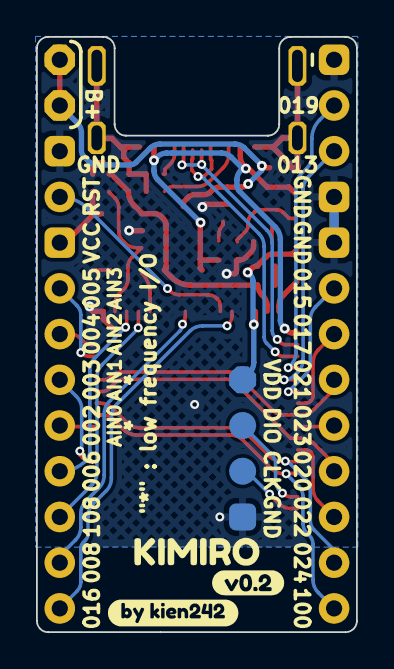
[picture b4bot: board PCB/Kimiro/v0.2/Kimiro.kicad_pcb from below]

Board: 2 copper layers, 17.8 x 33.1 mm, 28 parts (4 on the bottom side), 38 nets.

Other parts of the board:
kibuzzard-62E2A6C4: G***; kibuzzard-62E2A6C4
kibuzzard-62E24B57: G***; kibuzzard-62E24B57
kibuzzard-62E126A5: G***; kibuzzard-62E126A5
kibuzzard-62E129EE: G***; kibuzzard-62E129EE

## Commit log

2022-03-15 Doi ten mach tu Sakura thanh Kimiro
2022-03-15 v1.0 đã hoàn thành, cần tạo proto
2022-03-15 xóa #auto_saved_file#
2022-03-15 20:00 15/03/2022
2022-03-15 cập nhật PCB
2022-03-22 19:28 22/03/2022
2022-03-26 09:28 26/03/2022
2022-03-30 10:42 30/03/2022
2022-05-02 Cap nhat
2022-06-03 cap nhat bootloader
2022-06-08 cập nhật 12:21 08/06/2022
2022-07-28 Thêm v0.2
2022-08-02 Cập nhật file PCB
2022-08-05 Cập nhật: - Thêm flashbed cho nrfpill - Thay đổi GPIO Kimiro
2022-09-15 Update nRFpill
2022-10-02 Update kimỉo
2022-12-14 Add module
2023-03-19 Update bootloader.hex, flashbed.kicad_pcb, and 54 more files...
